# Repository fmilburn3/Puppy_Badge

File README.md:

# Puppy_Badge
KiCad Files for a Puppy Badge that blinks an LED using a 555 timer

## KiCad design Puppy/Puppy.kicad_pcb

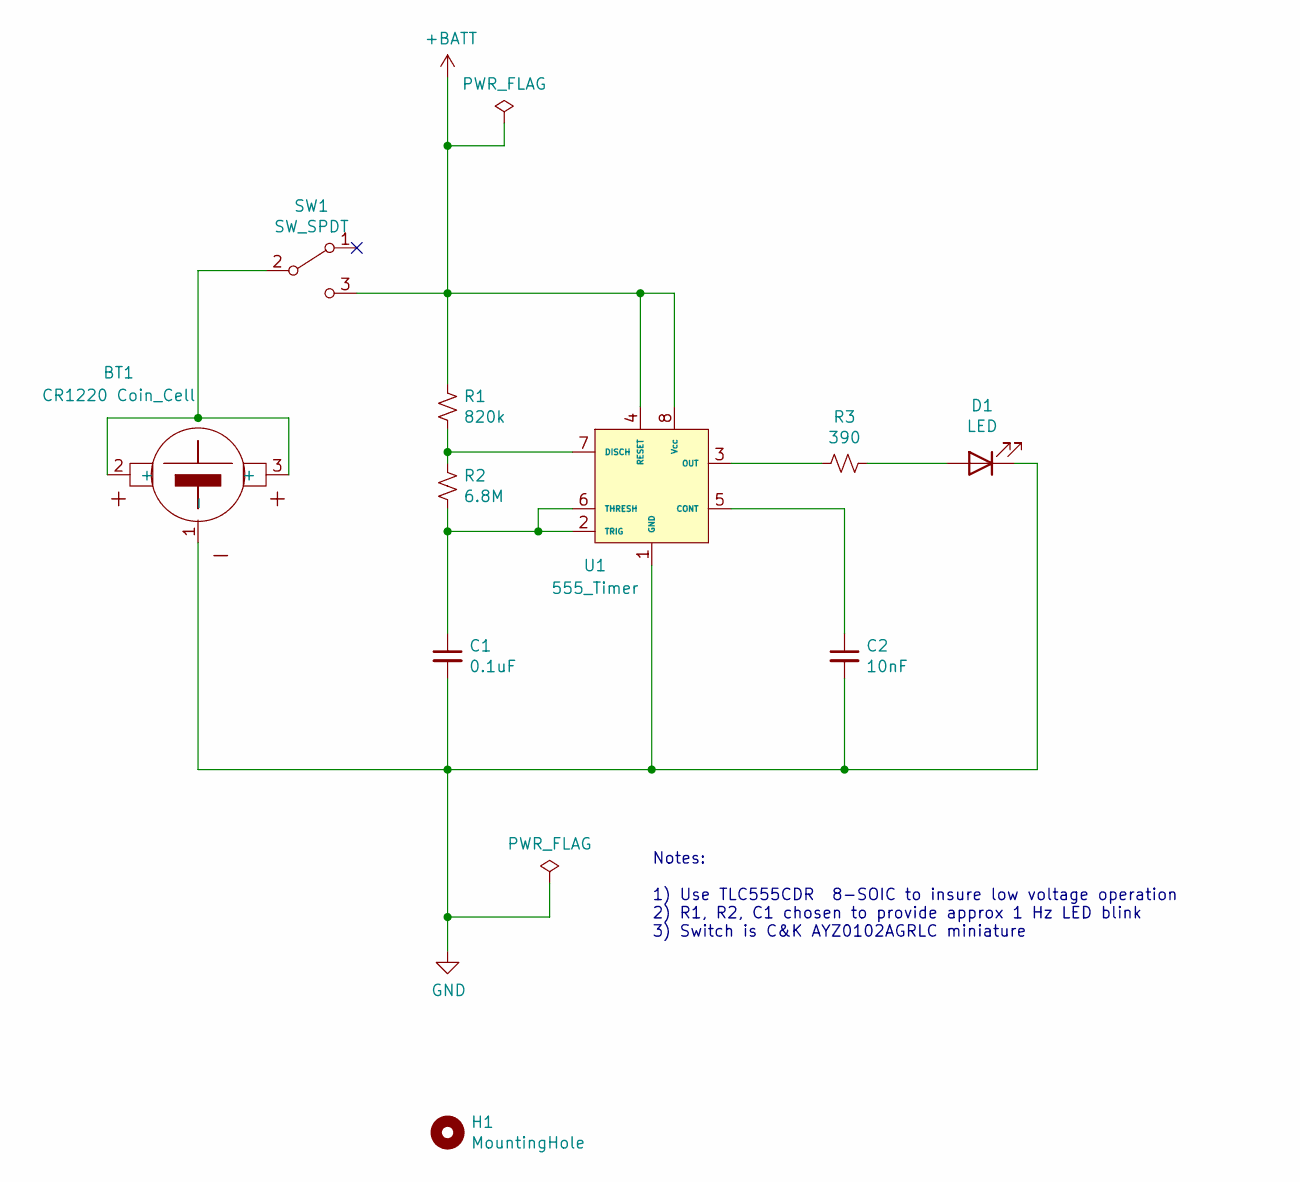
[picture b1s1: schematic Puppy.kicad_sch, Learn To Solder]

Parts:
BT1: CR1220 Coin_Cell; Keystone_3002_1x2032
C1: 0.1uF; R_0805_2012Metric_Pad1.15x1.40mm_HandSolder
C2: 10nF; R_0805_2012Metric_Pad1.15x1.40mm_HandSolder
D1: LED; R_0805_2012Metric_Pad1.15x1.40mm_HandSolder
H1: MountingHole; MountingHole_3.2mm_M3
R1: 820k; R_0805_2012Metric_Pad1.15x1.40mm_HandSolder
R2: 6.8M; R_0805_2012Metric_Pad1.15x1.40mm_HandSolder
R3: 390; R_0805_2012Metric_Pad1.15x1.40mm_HandSolder
SW1: SW_SPDT; CK_0102AGRLC_Slide_Switch
U1: 555_Timer; SOIC-8_3.9x4.9mm_P1.27mm

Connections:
+BATT: R1.1, SW1.3 (C), U1.4 (RESET), U1.8 (Vcc)
GND: BT1.1 (-), C1.2, C2.2, D1.1 (K), U1.1 (GND)
unnamed: BT1.2 (+), BT1.3 (+), SW1.2 (B)
unnamed: C1.1, R2.2, U1.2 (TRIG), U1.6 (THRESH)
unnamed: C2.1, U1.5 (CONT)
unnamed: D1.2 (A), R3.1
unnamed: R1.2, R2.1, U1.7 (DISCH)
unnamed: R3.2, U1.3 (OUT)

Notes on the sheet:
Notes: 1) Use TLC555CDR 8-SOIC to insure low voltage operation 2) R1, R2, C1 chosen to provide approx 1 Hz LED blink 3) Switch is C&K AYZ0102AGRLC miniature

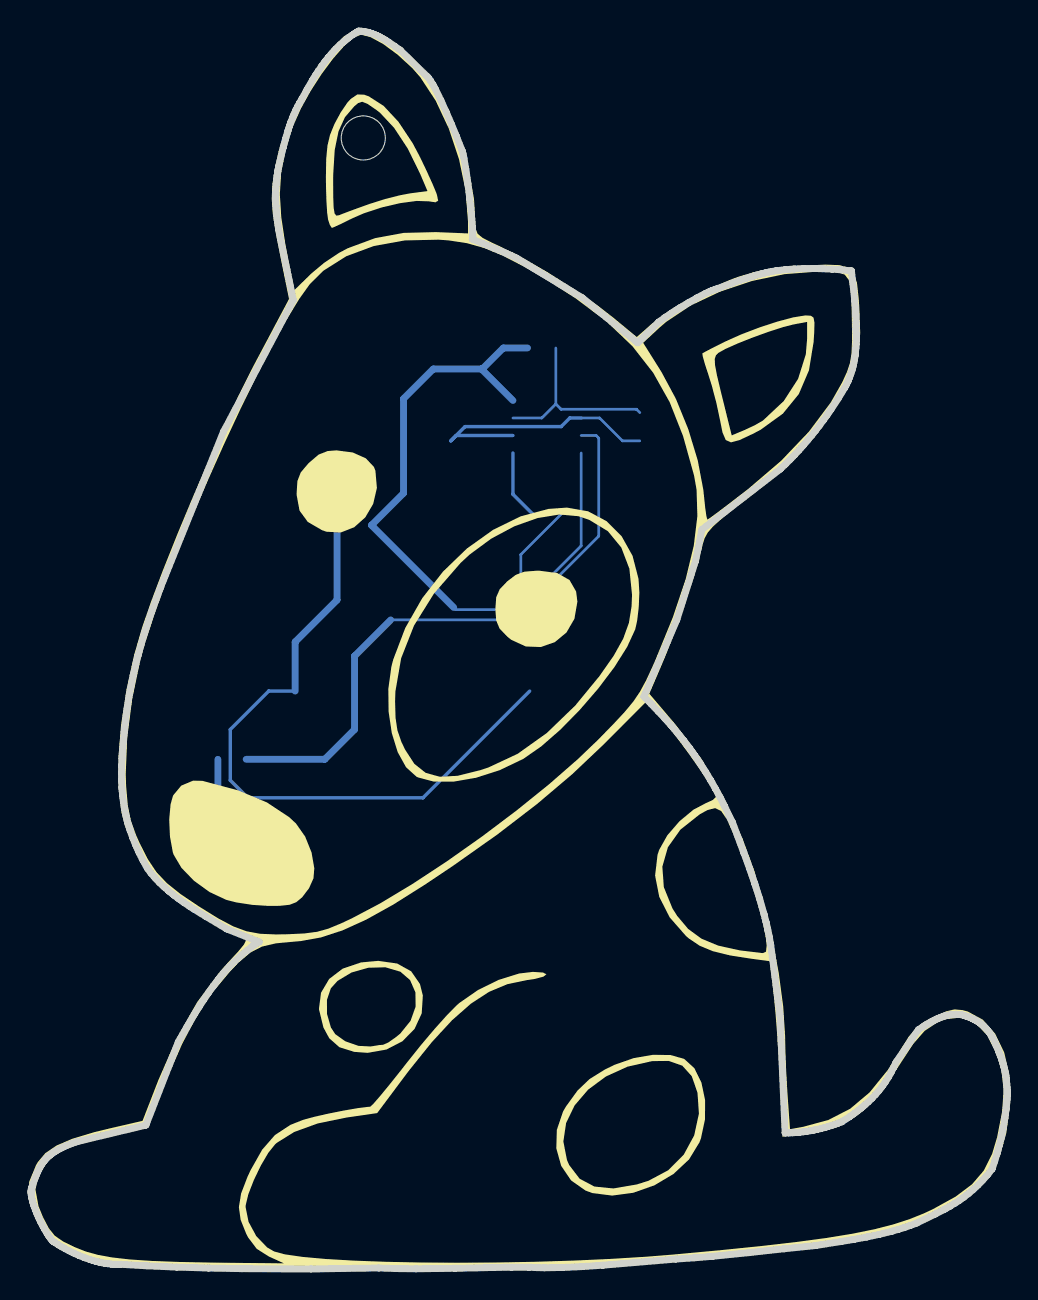
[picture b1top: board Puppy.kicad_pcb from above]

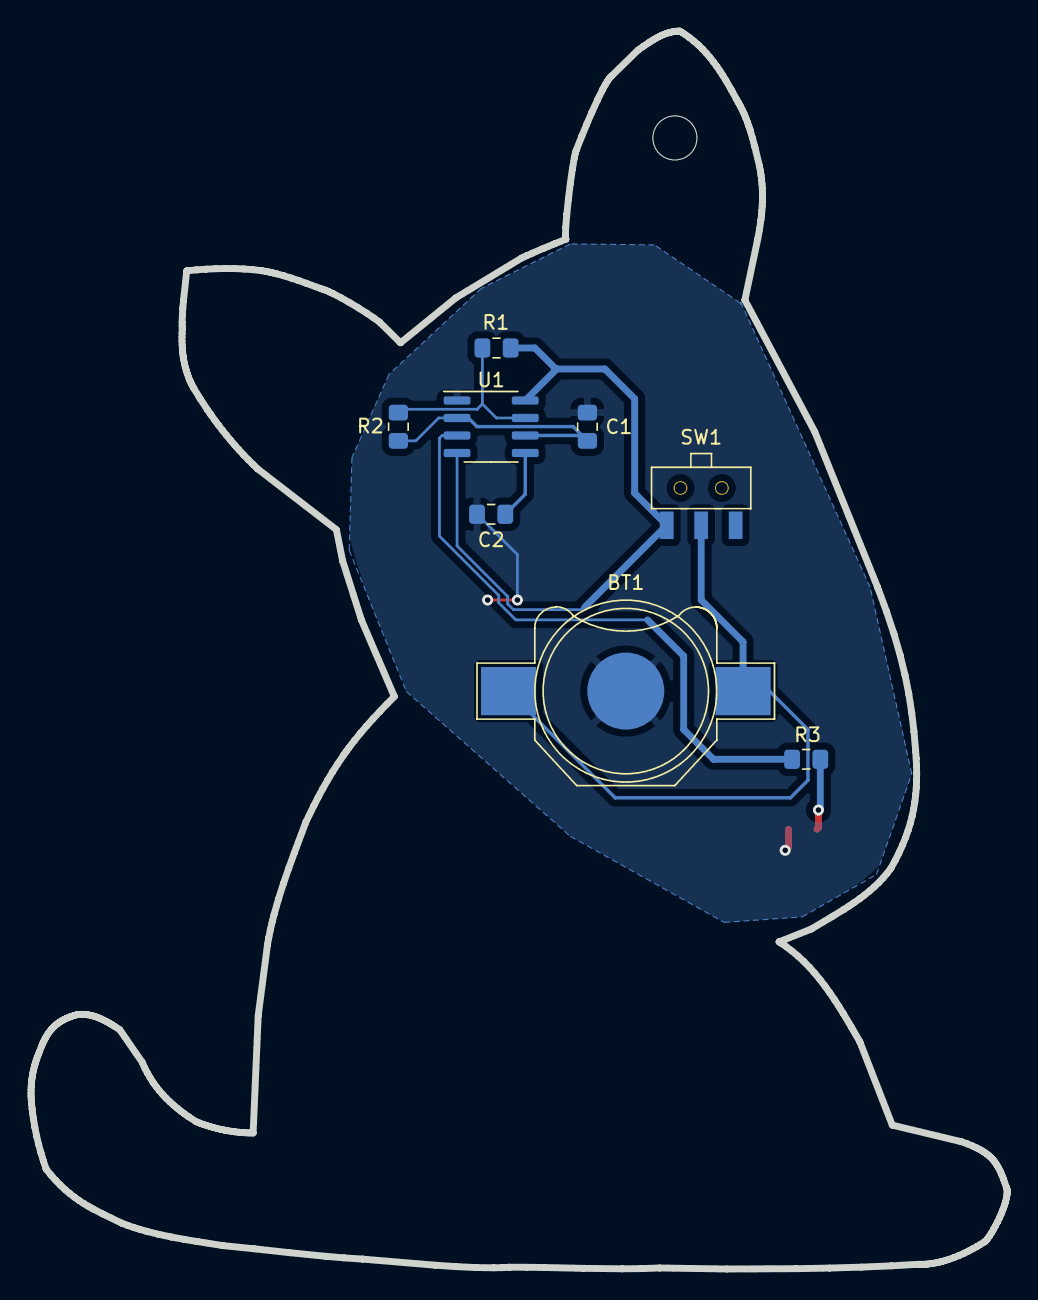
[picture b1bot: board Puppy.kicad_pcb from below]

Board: 2 copper layers, 70.8 x 89.8 mm, 10 parts (8 on the bottom side), 8 nets.

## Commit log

2022-08-18 Add files via upload
    Download and open Puppy.kicad_pro with KiCad to view. This design has not been sent to a PCB fab for manufacture at the time of posting. Extraneous files are present.
